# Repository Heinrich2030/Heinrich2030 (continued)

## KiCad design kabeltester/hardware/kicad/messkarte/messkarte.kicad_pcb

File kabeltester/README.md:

# Kabeltester – Tischgerät mit 7″-Touchdisplay

Kompakter Kabel- und Kabelbaumtester mit **128 Testpunkten (erweiterbar auf 256)**,
**4-Leiter-Widerstandsmessung bis 0,1 mΩ Auflösung** und großem Touchdisplay.
Jeder Testpunkt ist gleichzeitig Ein- und Ausgang – es gibt keine feste Aufteilung.

```
        ┌───────────────────────────────────────────┐
       ╱   [ A ▭▭▭▭▭▭▭▭ ]      [ B ▭▭▭▭▭▭▭▭ ]       ╱│   ← Adapterschächte (je 64 Pins)
      ╱───────────────────────────────────────────╱ │
     ╱  ┌─────────────────────────────┐   ( ● )  ╱  │   ← Start-Taster
    ╱   │   7″ Touch  800 × 480       │   ▮ ▮   ╱   │   ← Gut/Fehler-Leuchte
   ╱    │   GUT ✔  Cat6 1:1  2,1 s    │        ╱    │
  ╱     └─────────────────────────────┘       ╱    ╱
 └────────────────────────────────────────────┘   ╱      ca. 250 × 200 × 88 mm
 └────────────────────────────────────────────┘──╱
```

## Hardware-Auswahl (Kurzfassung)

| Baugruppe | Bauteil | Warum |
|---|---|---|
| Display + Bedienung | **Waveshare ESP32-S3-Touch-LCD-7** (7″, 800×480, kapazitiv) | großes Display, WLAN, 8 MB PSRAM, günstig (ca. 45 €) |
| Messsteuerung | **Raspberry Pi Pico 2 (RP2350)** | viele GPIO, schnelles SPI + ADC, ca. 6 € |
| Präzisionsmessung | **TI ADS1220** 24 Bit + **REF5025** | mΩ-Auflösung, 50/60-Hz-Filter, Temperatursensor |
| Testpunkt-Matrix | **ADG1606** (Force, 4,5 Ω) + **CD74HCT4067** (Sense) | echte 4-Leiter-Messung an jedem Pin |
| Adapter-Schnittstelle | **DIN 41612 C, 96-polig** | robust; 64 Testpunkte + Erkennung + I²C pro Seite |

Ausführliche Begründung, Schaltungskonzept und Leistungsdaten: [docs/hardware.md](docs/hardware.md).
Stückliste mit Bestellnummern: [hardware/stueckliste.csv](hardware/stueckliste.csv).

**Kosten (Richtwert):** ca. 330 € für den Grundausbau mit 128 Pins, ca. +190 € für den
Vollausbau mit 256 Pins, ca. 5–15 € je Steckeradapter.

## Funktionen

**Prüfen**
- Automatisches Erkennen der kompletten Verdrahtung (alle Pins gegen alle) in ca. 80 ms.
- **Einlernen mit Referenzkabel** („Golden Sample“): Kabel einstecken, Namen eingeben, fertig.
- Gut/Schlecht-Prüfung mit großer grün/roter Anzeige, Ton und LED-Leuchte.
- Fehlerarten im Klartext: *Unterbrechung, Kurzschluss, Vertauscht, Fehlverdrahtung,
  Widerstand zu hoch, hochohmiger Pfad (Feuchte/Schmutz), Diode/Halbleiter*.
- **Serienprüfung**: Kabel einstecken → Prüfung startet automatisch → abziehen → nächstes.
  Zähler für Gut/Fehler und Ausbeute in %.
- Start auch per Taster am Gerät oder **Fußschalter** (beide Hände frei).
- Optionale **Isolationsprüfung** zwischen allen Netzen (5 V, bis ca. 500 MΩ).

**Messen**
- 4-Leiter-Widerstandsmessung zwischen zwei beliebigen Pins, 0,1 mΩ … 200 kΩ, automatische
  Bereichswahl.
- **Stromumkehr**: hebt Thermospannungen auf und erkennt Dioden inkl. Polarität.
- **Längenberechnung** aus dem Widerstand (Kupfer, Querschnitt in mm² oder AWG),
  temperaturkompensiert über den Temperatursensor des ADC.
- **Nullabgleich** mit Kurzschlussadapter – Restwiderstände pro Pin werden gespeichert.

**Wackeltest**
- Überwacht alle gefundenen Verbindungen mit mehreren kHz und meldet jeden Aussetzer mit
  Dauer in µs – findet Wackelkontakte und Kabelbrüche, die beim normalen Test durchrutschen.

**Daten**
- Prüfprofile und Prüfprotokoll (CSV) im internen Flash.
- WLAN-Access-Point „Kabeltester“: Protokolle herunterladen, Profile hoch-/herunterladen im Browser.
- Profile als lesbare Textdateien, z. B.:
  ```
  KABELPROFIL 1
  name=Cat6 1:1
  pins=128
  durchgang=10
  isolation=10000000
  A1-B1 0.5
  A2-B2 0.5
  ```
- **Adapter-Erkennung**: Jeder Adapter trägt ein kleines EEPROM mit seinem Namen
  (z. B. „RJ45 8P8C“), der im Display angezeigt wird.
- **Fremdspannungsschutz**: Vor jeder Messung wird jeder Pin auf Spannung geprüft.

## Projektstruktur

```
kabeltester/
├── docs/hardware.md          Schaltungskonzept, Bauteilwahl, Leistungsdaten, Schutzkonzept
├── docs/adapter.md           Steckeradapter und Kurzschlussadapter bauen
├── hardware/stueckliste.csv  Stückliste mit Bestellnummern und Richtpreisen
├── hardware/kicad/           KiCad-Projekte: Schaltpläne, Platinen, Gerber, STEP (Generator in Python)
├── gehaeuse/step/            Gehäuse und Gesamtbaugruppe als STEP/STL (für jedes CAD-Programm)
├── gehaeuse/gehaeuse.scad    Pultgehäuse für den 3D-Druck (OpenSCAD, parametrisch)
├── docs/zusammenbau-3d.html  Drehbares 3D-Modell des Zusammenbaus mit Explosionsansicht (im Browser öffnen)
├── firmware/common/          Analyse-Kern (Soll/Ist-Vergleich, Profile, Länge) – auf PC testbar
├── firmware/messkarte/       Pico 2: Matrix, ADS1220, Messverfahren, Textprotokoll
├── firmware/display/         ESP32-S3: LVGL-Oberfläche, Profile, Protokoll, Weboberfläche
└── tests/                    PC-Tests für den Analyse-Kern
```

## Bauen und Flashen

Beide Firmwares sind PlatformIO-Projekte.

Messkarte (Pico 2 per USB im BOOTSEL-Modus anschließen):

```bash
cd kabeltester/firmware/messkarte && pio run -t upload
```

Display-Einheit: Zuerst `lvgl_port_v8.cpp` und `lvgl_port_v8.h` aus dem Waveshare-Beispiel
„lvgl_v8_port“ (Waveshare-Wiki zum ESP32-S3-Touch-LCD-7) nach `firmware/display/src/`
kopieren. Dann:

```bash
cd kabeltester/firmware/display && pio run -t upload
```

Tests des Analyse-Kerns auf dem PC:

```bash
make -C kabeltester/tests
```

Die Messkarte lässt sich auch ohne Display über USB bedienen (Terminal, 115 200 Baud), z. B.
`SCAN`, `R A1 B1`, `INFO`. Alle Befehle stehen am Anfang von
[`firmware/messkarte/src/main.cpp`](firmware/messkarte/src/main.cpp).

## Inbetriebnahme

1. Messkarte ohne Kanalkarten flashen, `INFO` per USB prüfen (Temperatur plausibel?).
2. Kanalkarten anschließen, `SCAN` ohne Adapter → keine Verbindungen.
3. Kurzschlussadapter auf Seite A und/oder B stecken → im Setup „Nullabgleich“ (oder `KAL NULL`).
   Jede Seite mit gestecktem Kurzschlussadapter wird einzeln abgeglichen, die anderen bleiben.
4. Präzisionswiderstände (z. B. 0,1 Ω / 10 Ω / 1 kΩ / 100 kΩ, 0,1 %) messen und mit den
   Leistungsdaten in `docs/hardware.md` vergleichen.

## Stand und offene Punkte

- Schaltpläne und Platinen-Platzierung in KiCad sind fertig, ebenso Gehäuse und Baugruppe als STEP.
  **Die Leiterbahnen fehlen noch** – siehe [hardware/kicad/README.md](hardware/kicad/README.md).
- Einige Pinbelegungen eigener Symbole und die DIN-41612-Ausrichtung sind vor der Bestellung zu prüfen
  (Liste in der KiCad-Anleitung).
- Die Firmware ist gegen die Bibliotheken syntaktisch geprüft, aber noch nicht auf echter Hardware
  gelaufen. Die Leistungsdaten sind berechnete Richtwerte.
- Die eingebauten LVGL-Schriften haben keine Umlaute; die Oberfläche schreibt daher „ue/oe“.

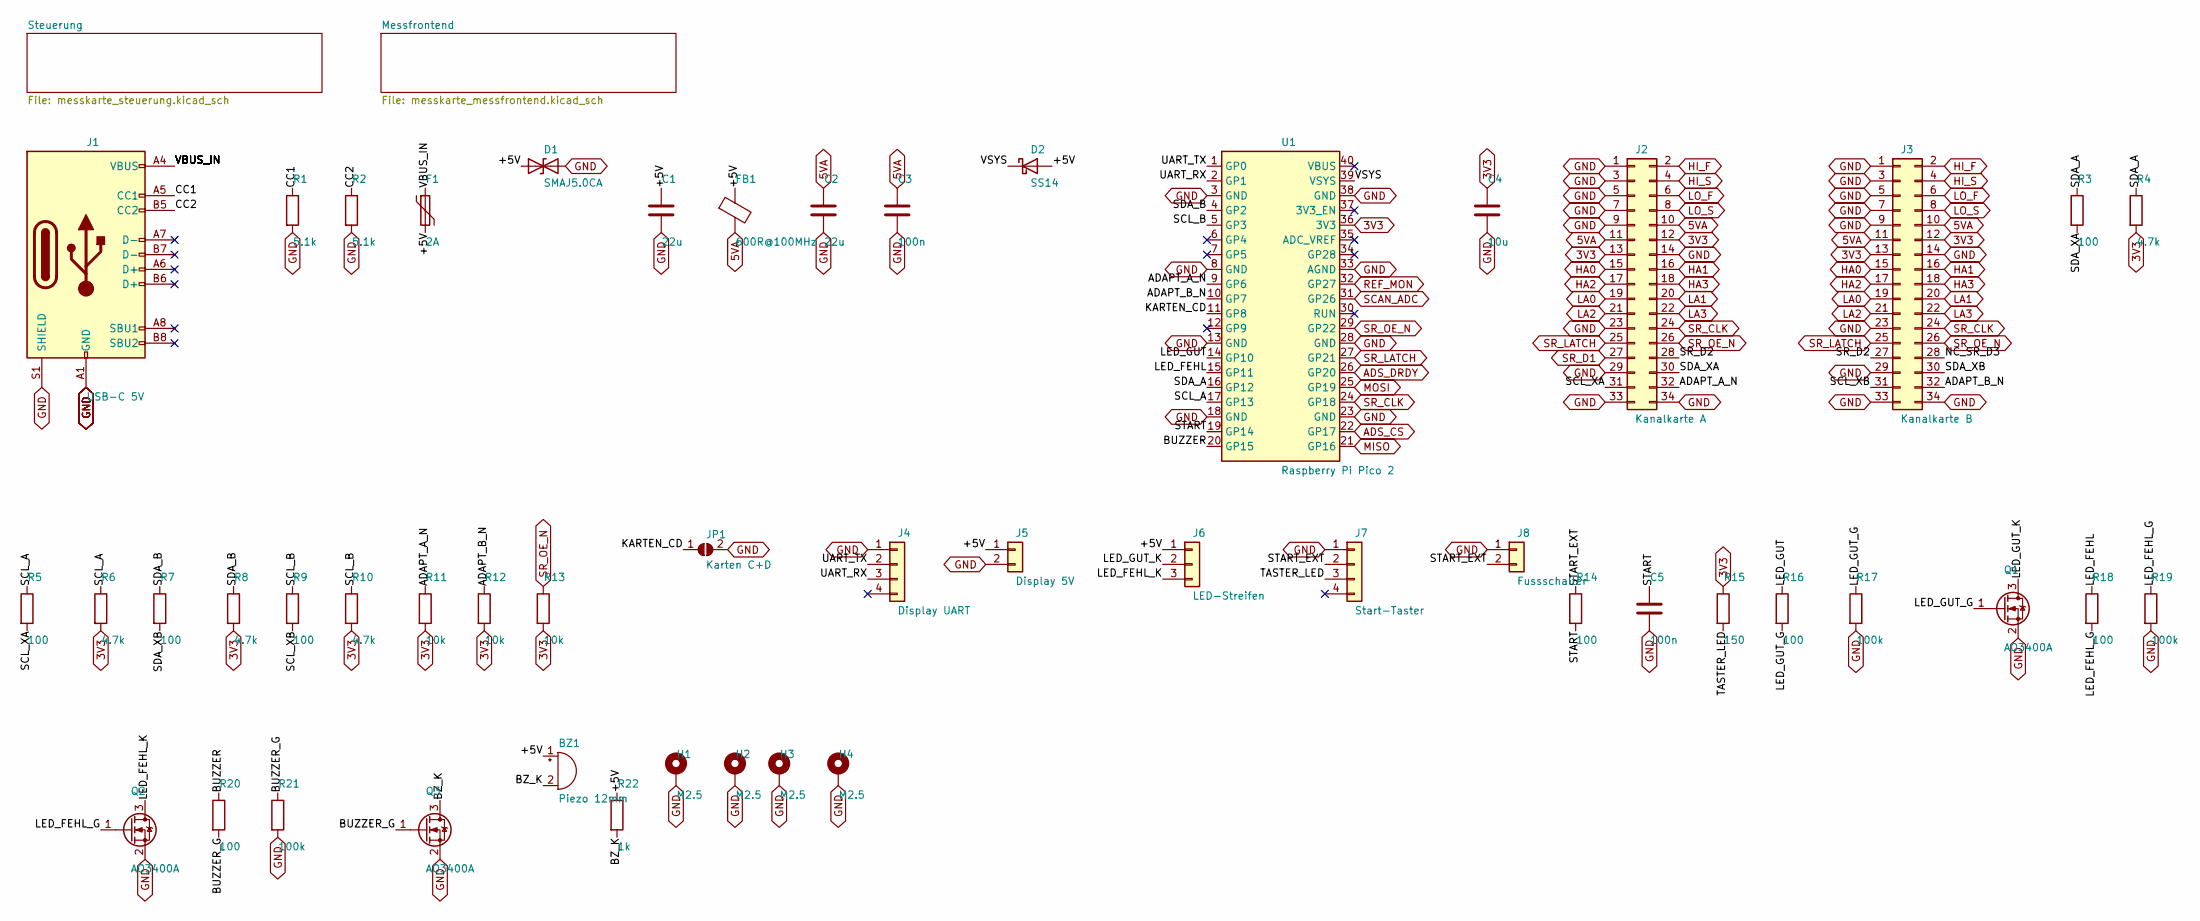
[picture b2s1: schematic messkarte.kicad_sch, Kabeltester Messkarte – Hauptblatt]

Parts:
BZ1: Piezo 12mm; Buzzer_12x9.5RM7.6; MPN TDK PS1240P02BT
C1, C2: 22u; C_1206_3216Metric
C3, C5: 100n; C_0603_1608Metric; LCSC C14663
C4: 10u; C_0805_2012Metric; LCSC C15850
D1: SMAJ5.0CA; D_SMA
D2: SS14; D_SMA; LCSC C2480
F1: 2A; Fuse_1812_4532Metric
FB1: 600R@100MHz; L_0805_2012Metric
H1, H2, H3, H4: M2.5; MountingHole_2.7mm_M2.5_Pad_Via
J1: USB-C 5V; USB_C_Receptacle_GCT_USB4105-xx-A_16P_TopMnt_Horizontal; MPN GCT USB4105-GF-A
J2: Kanalkarte A; IDC-Header_2x17_P2.54mm_Vertical
J3: Kanalkarte B; IDC-Header_2x17_P2.54mm_Vertical
J4: Display UART; JST_PH_B4B-PH-K_1x04_P2.00mm_Vertical
J5: Display 5V; JST_PH_B2B-PH-K_1x02_P2.00mm_Vertical
J6: LED-Streifen; JST_PH_B3B-PH-K_1x03_P2.00mm_Vertical
J7: Start-Taster; JST_PH_B4B-PH-K_1x04_P2.00mm_Vertical
J8: Fussschalter; JST_PH_B2B-PH-K_1x02_P2.00mm_Vertical
JP1: Karten C+D; SolderJumper-2_P1.3mm_Open_RoundedPad1.0x1.5mm
Q1, Q2, Q3: AO3400A; SOT-23; LCSC C20917
R1, R2: 5.1k; R_0603_1608Metric; LCSC C23186
R3, R5, R7, R9, R14, R16, R18, R20: 100; R_0603_1608Metric; LCSC C22775
R4, R6, R8, R10: 4.7k; R_0603_1608Metric; LCSC C23162
R11, R12, R13: 10k; R_0603_1608Metric; LCSC C25804
R15: 150; R_0603_1608Metric
R17, R19, R21: 100k; R_0603_1608Metric; LCSC C25803
R22: 1k; R_0603_1608Metric; LCSC C21190
U1: Raspberry Pi Pico 2; RaspberryPi_Pico2_THT; MPN Raspberry Pi SC1631

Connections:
3V3: C4.1, J2.12, J2.13, J3.12, J3.13, R4.2, R6.2, R8.2, R10.2, R11.2, R12.2, R13.2, R15.1, U1.36 (3V3); also elsewhere on the board
5VA: C2.1, C3.1, FB1.2, J2.10, J2.11, J3.10, J3.11; also elsewhere on the board
+5V: BZ1.1 (+), C1.1, D1.1 (A1), D2.2 (A), F1.2, FB1.1, J5.1, J6.1, R22.1
ADAPT_A_N: J2.32, R11.1, U1.9 (GP6)
ADAPT_B_N: J3.32, R12.1, U1.10 (GP7)
ADS_CS: U1.22 (GP17); also elsewhere on the board
ADS_DRDY: U1.26 (GP20); also elsewhere on the board
BUZZER: R20.1, U1.20 (GP15)
BUZZER_G: Q3.1 (G), R20.2, R21.1
BZ_K: BZ1.2 (-), Q3.3 (D), R22.2
CC1: J1.A5 (CC1), R1.1
CC2: J1.B5 (CC2), R2.1
GND: C1.2, C2.2, C3.2, C4.2, C5.2, D1.2 (A2), H1.1, H2.1, H3.1, H4.1, J1.A1 (GND), J1.A12 (GND), J1.B1 (GND), J1.B12 (GND), J1.S1 (SHIELD), J2.1, J2.3, J2.5, J2.7, J2.9, J2.14, J2.23, J2.29, J2.33, J2.34, J3.1, J3.3, J3.5, J3.7, J3.9, J3.14, J3.23, J3.29, J3.33, J3.34, J4.1, J5.2, J7.1, J8.1, JP1.2 (B), Q1.2 (S), Q2.2 (S), Q3.2 (S), R1.2, R2.2, R17.2, R19.2, R21.2, U1.3 (GND), U1.8 (GND), U1.13 (GND), U1.18 (GND), U1.23 (GND), U1.28 (GND), U1.33 (AGND), U1.38 (GND); also elsewhere on the board
HA0: J2.15, J3.15; also elsewhere on the board
HA1: J2.16, J3.16; also elsewhere on the board
HA2: J2.17, J3.17; also elsewhere on the board
HA3: J2.18, J3.18; also elsewhere on the board
HI_F: J2.2, J3.2; also elsewhere on the board
HI_S: J2.4, J3.4; also elsewhere on the board
KARTEN_CD: JP1.1 (A), U1.11 (GP8)
LA0: J2.19, J3.19; also elsewhere on the board
LA1: J2.20, J3.20; also elsewhere on the board
LA2: J2.21, J3.21; also elsewhere on the board
LA3: J2.22, J3.22; also elsewhere on the board
LED_FEHL: R18.1, U1.15 (GP11)
LED_FEHL_G: Q2.1 (G), R18.2, R19.1
LED_FEHL_K: J6.3, Q2.3 (D)
LED_GUT: R16.1, U1.14 (GP10)
LED_GUT_G: Q1.1 (G), R16.2, R17.1
LED_GUT_K: J6.2, Q1.3 (D)
LO_F: J2.6, J3.6; also elsewhere on the board
LO_S: J2.8, J3.8; also elsewhere on the board
MISO: U1.21 (GP16); also elsewhere on the board
MOSI: U1.25 (GP19); also elsewhere on the board
NC_SR_D3: J3.28
REF_MON: U1.32 (GP27); also elsewhere on the board
SCAN_ADC: U1.31 (GP26); also elsewhere on the board
SCL_A: R5.1, R6.1, U1.17 (GP13)
SCL_B: R9.1, R10.1, U1.5 (GP3)
SCL_XA: J2.31, R5.2
SCL_XB: J3.31, R9.2
SDA_A: R3.1, R4.1, U1.16 (GP12)
SDA_B: R7.1, R8.1, U1.4 (GP2)
SDA_XA: J2.30, R3.2
SDA_XB: J3.30, R7.2
SR_CLK: J2.24, J3.24, U1.24 (GP18); also elsewhere on the board
SR_D1: J2.27; also elsewhere on the board
SR_D2: J2.28, J3.27
SR_LATCH: J2.25, J3.25, U1.27 (GP21); also elsewhere on the board
SR_OE_N: J2.26, J3.26, R13.1, U1.29 (GP22); also elsewhere on the board
START: C5.1, R14.2, U1.19 (GP14)
START_EXT: J7.2, J8.2, R14.1
TASTER_LED: J7.3, R15.2
UART_RX: J4.3, U1.2 (GP1)
UART_TX: J4.2, U1.1 (GP0)
VBUS_IN: F1.1, J1.A4 (VBUS), J1.A9 (VBUS), J1.B4 (VBUS), J1.B9 (VBUS)
VSYS: D2.1 (K), U1.39 (VSYS)

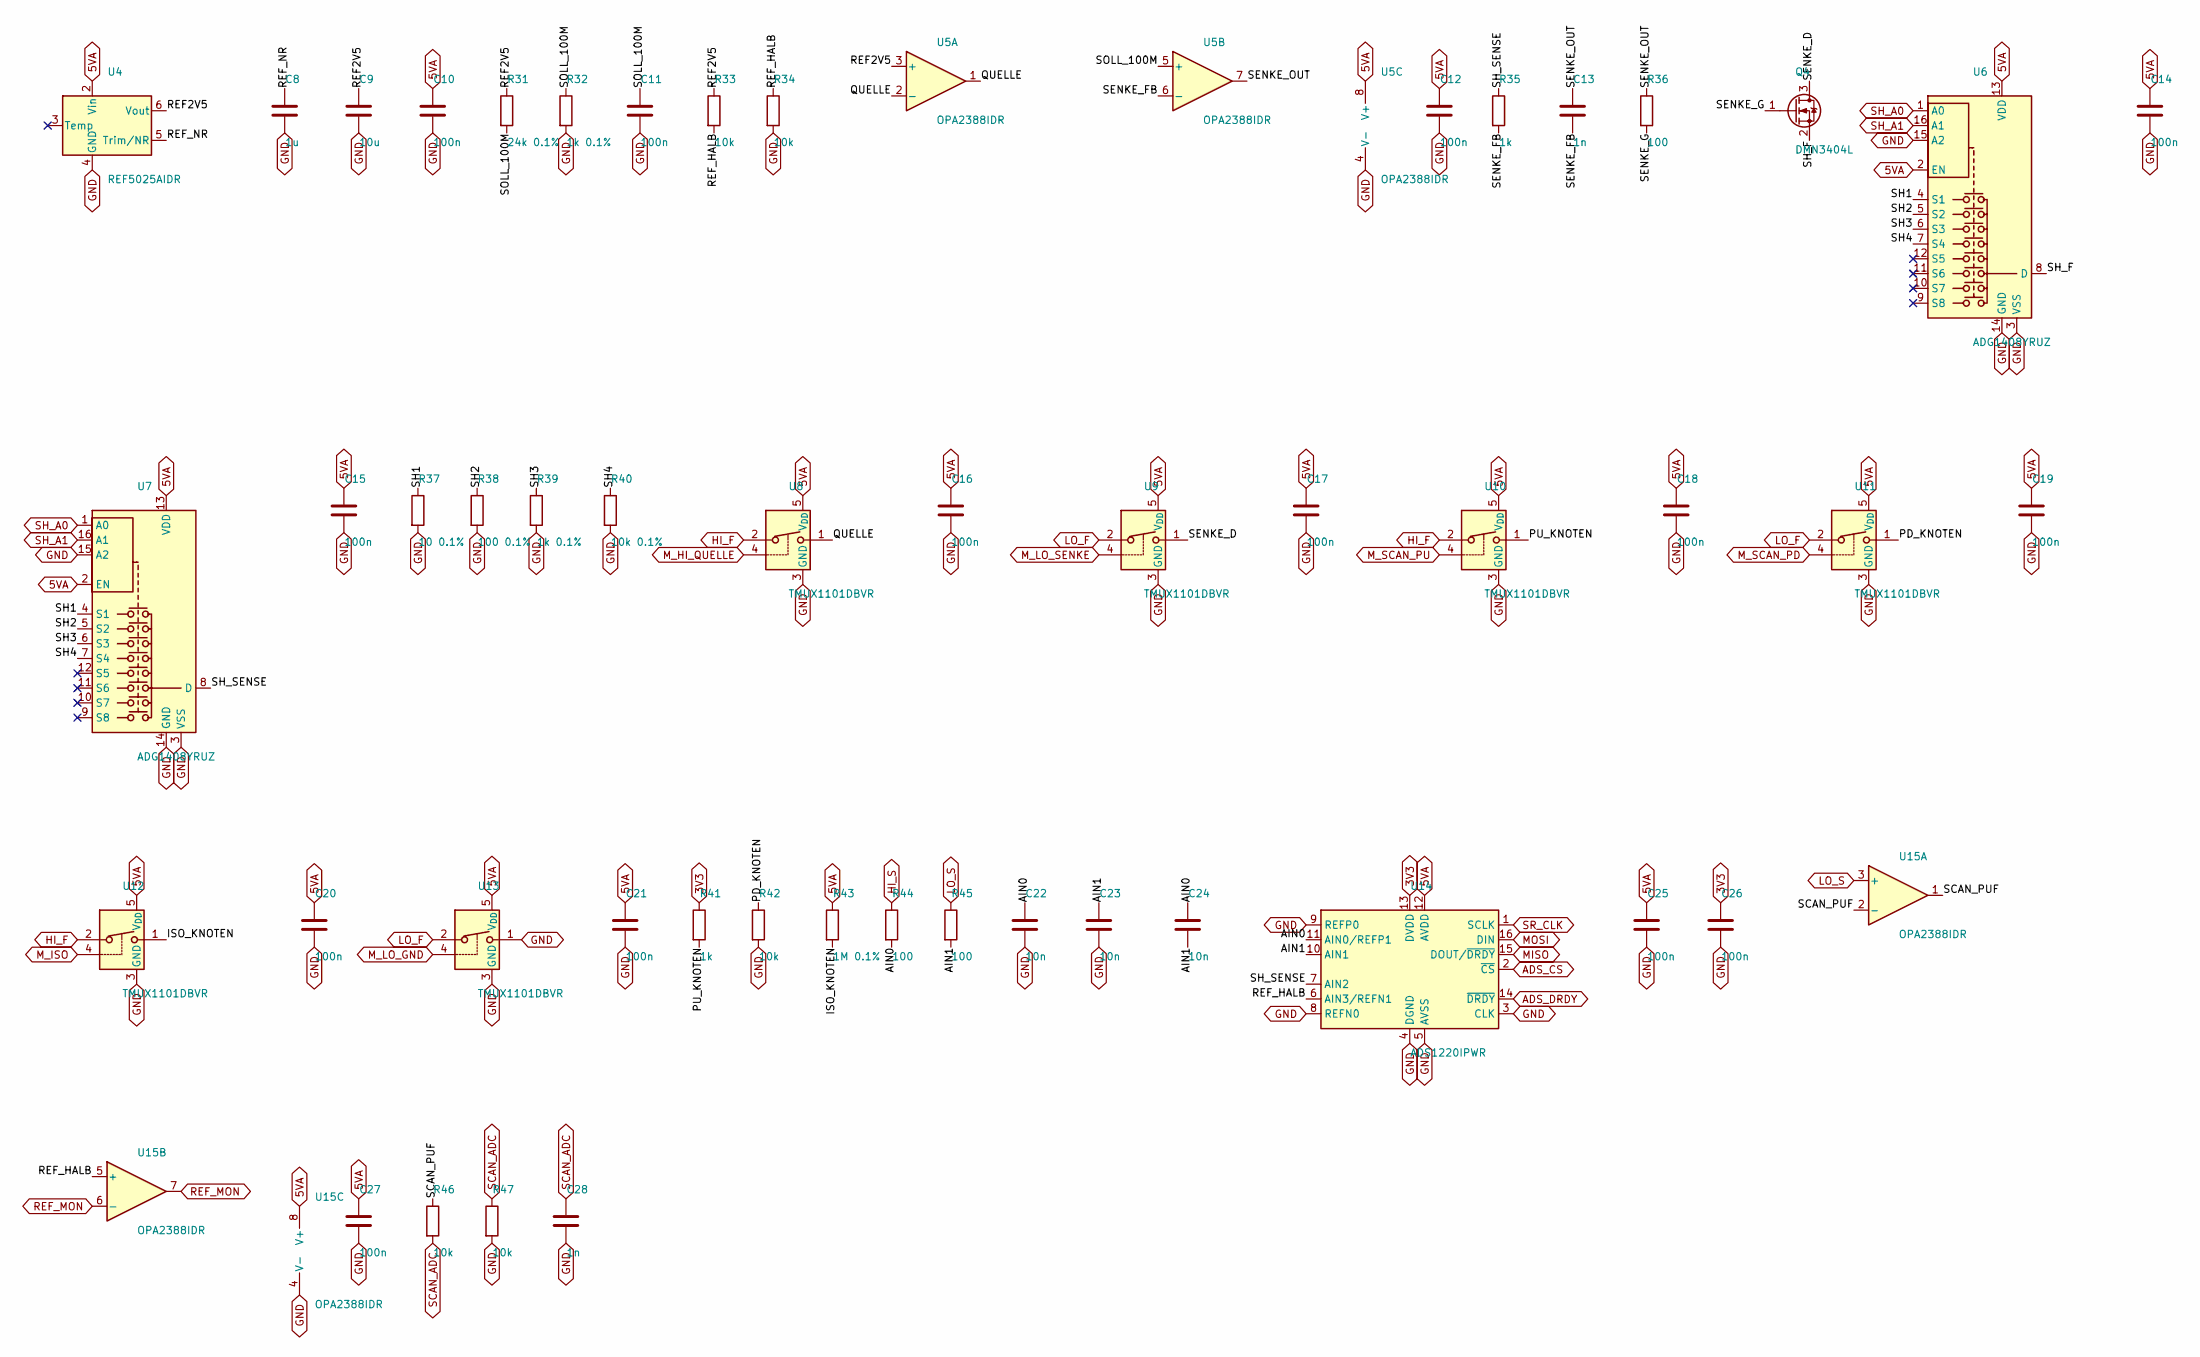
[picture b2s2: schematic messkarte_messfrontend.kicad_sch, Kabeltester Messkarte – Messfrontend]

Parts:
C8: 1u; C_0603_1608Metric; LCSC C15849
C9: 10u; C_0805_2012Metric; LCSC C15850
C10, C11, C12, C14, C15, C16, C17, C18, C19, C20, C21, C25, C26, C27: 100n; C_0603_1608Metric; LCSC C14663
C13, C28: 1n; C_0603_1608Metric; LCSC C1588
C22, C23, C24: 10n; C_0603_1608Metric; LCSC C57112
Q4: DMN3404L; SOT-23
R31: 24k 0.1%; R_0603_1608Metric
R32: 1k 0.1%; R_0603_1608Metric; LCSC C21190
R33, R34, R42, R46, R47: 10k; R_0603_1608Metric; LCSC C25804
R35, R41: 1k; R_0603_1608Metric; LCSC C21190
R36, R44, R45: 100; R_0603_1608Metric; LCSC C22775
R37: 10 0.1%; R_0805_2012Metric; MPN Vishay TNPW0805 0.1% 10ppm
R38: 100 0.1%; R_0805_2012Metric; MPN Vishay TNPW0805 0.1% 10ppm
R39: 1k 0.1%; R_0805_2012Metric; MPN Vishay TNPW0805 0.1% 10ppm
R40: 10k 0.1%; R_0805_2012Metric; MPN Vishay TNPW0805 0.1% 10ppm
R43: 1M 0.1%; R_0805_2012Metric; MPN Vishay TNPW08051M00BEEA
U4: REF5025AIDR; SOIC-8_3.9x4.9mm_P1.27mm
U5, U15: OPA2388IDR; SOIC-8_3.9x4.9mm_P1.27mm
U6, U7: ADG1408YRUZ; TSSOP-16_4.4x5mm_P0.65mm
U8, U9, U10, U11, U12, U13: TMUX1101DBVR; SOT-23-5
U14: ADS1220IPWR; TSSOP-16_4.4x5mm_P0.65mm

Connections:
3V3: C26.1, R41.1, U14.13 (DVDD); also elsewhere on the board
5VA: C10.1, C12.1, C14.1, C15.1, C16.1, C17.1, C18.1, C19.1, C20.1, C21.1, C25.1, C27.1, R43.1, U4.2 (Vin), U5.8 (V+), U6.2 (EN), U6.13 (VDD), U7.2 (EN), U7.13 (VDD), U8.5 (V_{DD}), U9.5 (V_{DD}), U10.5 (V_{DD}), U11.5 (V_{DD}), U12.5 (V_{DD}), U13.5 (V_{DD}), U14.12 (AVDD), U15.8 (V+); also elsewhere on the board
ADS_CS: U14.2 (~CS); also elsewhere on the board
ADS_DRDY: U14.14 (~DRDY); also elsewhere on the board
AIN0: C22.1, C24.1, R44.2, U14.11 (AIN0/REFP1)
AIN1: C23.1, C24.2, R45.2, U14.10 (AIN1)
GND: C8.2, C9.2, C10.2, C11.2, C12.2, C14.2, C15.2, C16.2, C17.2, C18.2, C19.2, C20.2, C21.2, C22.2, C23.2, C25.2, C26.2, C27.2, C28.2, R32.2, R34.2, R37.2, R38.2, R39.2, R40.2, R42.2, R47.2, U4.4 (GND), U5.4 (V-), U6.3 (VSS), U6.14 (GND), U6.15 (A2), U7.3 (VSS), U7.14 (GND), U7.15 (A2), U8.3 (GND), U9.3 (GND), U10.3 (GND), U11.3 (GND), U12.3 (GND), U13.1, U13.3 (GND), U14.3 (CLK), U14.4 (DGND), U14.5 (AVSS), U14.8 (REFN0), U14.9 (REFP0), U15.4 (V-); also elsewhere on the board
HI_F: U8.2, U10.2, U12.2; also elsewhere on the board
HI_S: R44.1; also elsewhere on the board
ISO_KNOTEN: R43.2, U12.1
LO_F: U9.2, U11.2, U13.2; also elsewhere on the board
LO_S: R45.1, U15.3 (+); also elsewhere on the board
MISO: U14.15 (DOUT/~DRDY); also elsewhere on the board
MOSI: U14.16 (DIN); also elsewhere on the board
M_HI_QUELLE: U8.4; also elsewhere on the board
M_ISO: U12.4; also elsewhere on the board
M_LO_GND: U13.4; also elsewhere on the board
M_LO_SENKE: U9.4; also elsewhere on the board
M_SCAN_PD: U11.4; also elsewhere on the board
M_SCAN_PU: U10.4; also elsewhere on the board
PD_KNOTEN: R42.1, U11.1
PU_KNOTEN: R41.2, U10.1
QUELLE: U5.1, U5.2 (-), U8.1
REF2V5: C9.1, R31.1, R33.1, U4.6 (Vout), U5.3 (+)
REF_HALB: R33.2, R34.1, U14.6 (AIN3/REFN1), U15.5 (+)
REF_MON: U15.6 (-), U15.7; also elsewhere on the board
REF_NR: C8.1, U4.5 (Trim/NR)
SCAN_ADC: C28.1, R46.2, R47.1; also elsewhere on the board
SCAN_PUF: R46.1, U15.1, U15.2 (-)
SENKE_D: Q4.3 (D), U9.1
SENKE_FB: C13.2, R35.2, U5.6 (-)
SENKE_G: Q4.1 (G), R36.2
SENKE_OUT: C13.1, R36.1, U5.7
SH1: R37.1, U6.4 (S1), U7.4 (S1)
SH2: R38.1, U6.5 (S2), U7.5 (S2)
SH3: R39.1, U6.6 (S3), U7.6 (S3)
SH4: R40.1, U6.7 (S4), U7.7 (S4)
SH_A0: U6.1 (A0), U7.1 (A0); also elsewhere on the board
SH_A1: U6.16 (A1), U7.16 (A1); also elsewhere on the board
SH_F: Q4.2 (S), U6.8 (D)
SH_SENSE: R35.1, U7.8 (D), U14.7 (AIN2)
SOLL_100M: C11.1, R31.2, R32.1, U5.5 (+)
SR_CLK: U14.1 (SCLK); also elsewhere on the board

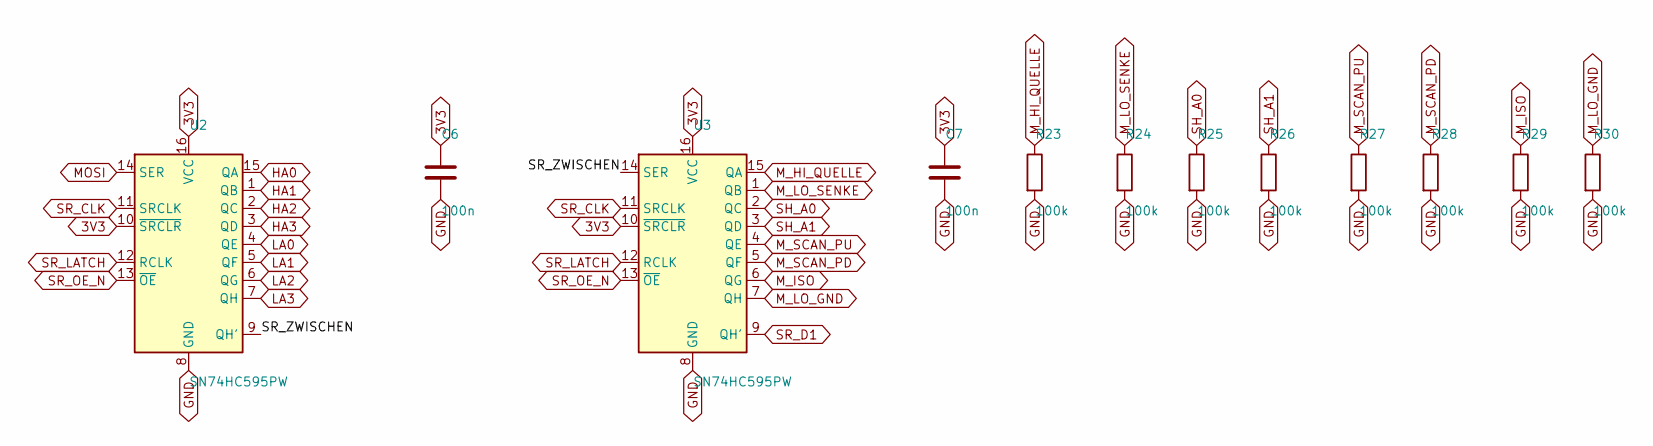
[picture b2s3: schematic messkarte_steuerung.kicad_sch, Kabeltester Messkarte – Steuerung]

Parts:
C6, C7: 100n; C_0603_1608Metric; LCSC C14663
R23, R24, R25, R26, R27, R28, R29, R30: 100k; R_0603_1608Metric; LCSC C25803
U2, U3: SN74HC595PW; TSSOP-16_4.4x5mm_P0.65mm; LCSC C5947

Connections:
3V3: C6.1, C7.1, U2.10 (~SRCLR), U2.16 (VCC), U3.10 (~SRCLR), U3.16 (VCC); also elsewhere on the board
GND: C6.2, C7.2, R23.2, R24.2, R25.2, R26.2, R27.2, R28.2, R29.2, R30.2, U2.8 (GND), U3.8 (GND); also elsewhere on the board
HA0: U2.15 (QA); also elsewhere on the board
HA1: U2.1 (QB); also elsewhere on the board
HA2: U2.2 (QC); also elsewhere on the board
HA3: U2.3 (QD); also elsewhere on the board
LA0: U2.4 (QE); also elsewhere on the board
LA1: U2.5 (QF); also elsewhere on the board
LA2: U2.6 (QG); also elsewhere on the board
LA3: U2.7 (QH); also elsewhere on the board
MOSI: U2.14 (SER); also elsewhere on the board
M_HI_QUELLE: R23.1, U3.15 (QA); also elsewhere on the board
M_ISO: R29.1, U3.6 (QG); also elsewhere on the board
M_LO_GND: R30.1, U3.7 (QH); also elsewhere on the board
M_LO_SENKE: R24.1, U3.1 (QB); also elsewhere on the board
M_SCAN_PD: R28.1, U3.5 (QF); also elsewhere on the board
M_SCAN_PU: R27.1, U3.4 (QE); also elsewhere on the board
SH_A0: R25.1, U3.2 (QC); also elsewhere on the board
SH_A1: R26.1, U3.3 (QD); also elsewhere on the board
SR_CLK: U2.11 (SRCLK), U3.11 (SRCLK); also elsewhere on the board
SR_D1: U3.9 (QH'); also elsewhere on the board
SR_LATCH: U2.12 (RCLK), U3.12 (RCLK); also elsewhere on the board
SR_OE_N: U2.13 (~OE), U3.13 (~OE); also elsewhere on the board
SR_ZWISCHEN: U2.9 (QH'), U3.14 (SER)

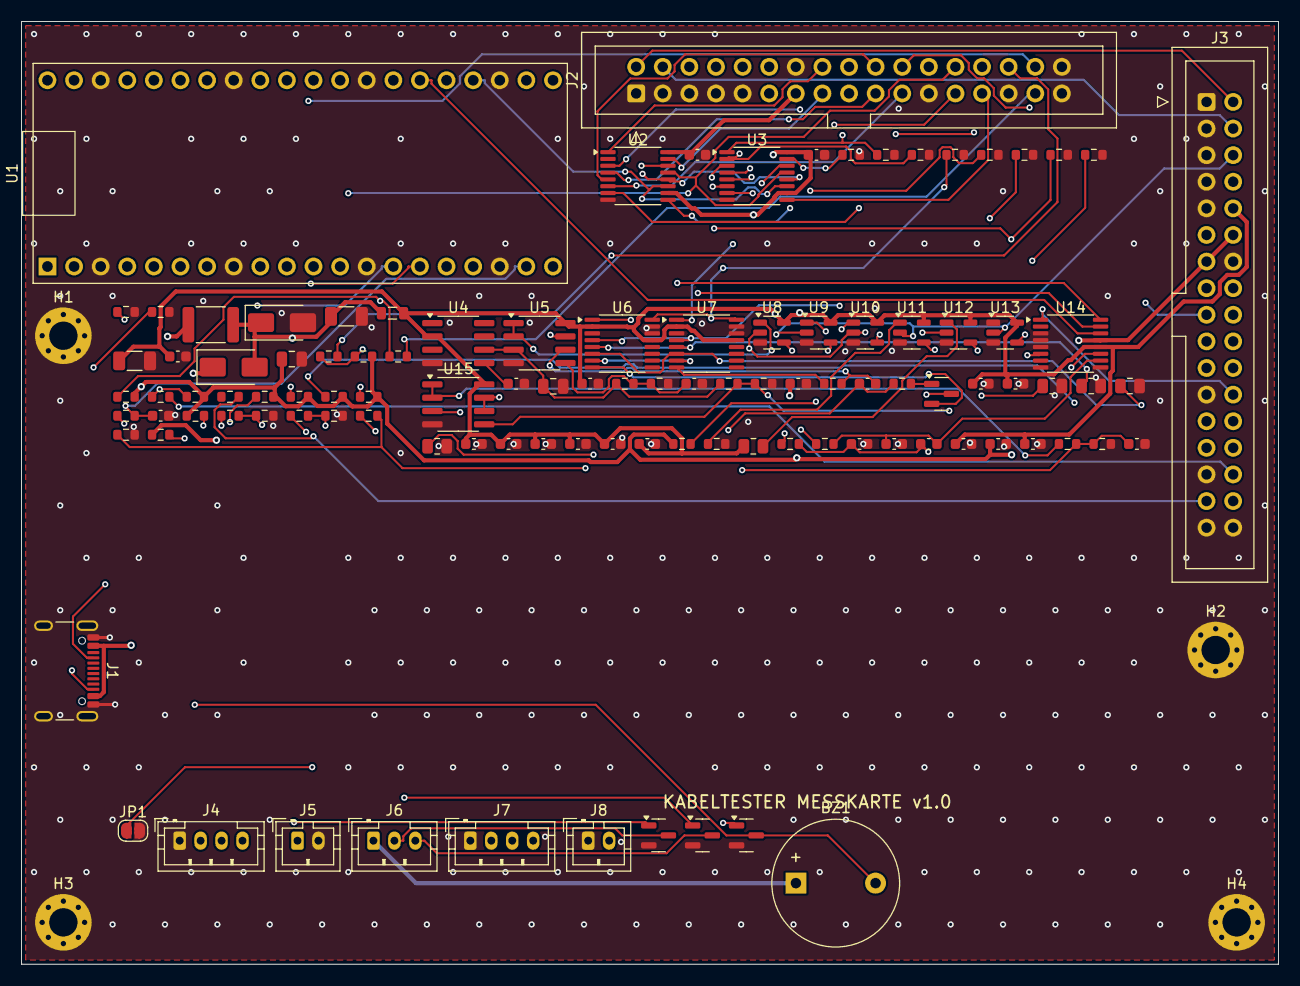
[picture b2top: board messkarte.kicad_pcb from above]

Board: 4 copper layers, 120.0 x 90.0 mm, 112 parts (0 on the bottom side), 86 nets.

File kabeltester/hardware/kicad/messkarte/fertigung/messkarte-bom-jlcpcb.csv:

Comment,Designator,Footprint,Menge,Hersteller-Nr.,LCSC Part #
Piezo 12mm,BZ1,Buzzer_12x9.5RM7.6,1,TDK PS1240P02BT,
100n,"C3,C5,C6,C7,C10,C11,C12,C14,C15,C16,C17,C18,C19,C20,C21,C25,C26,C27",C_0603_1608Metric,18,,C14663
10n,"C22,C23,C24",C_0603_1608Metric,3,,C57112
1n,"C13,C28",C_0603_1608Metric,2,,C1588
1u,C8,C_0603_1608Metric,1,,C15849
10u,"C4,C9",C_0805_2012Metric,2,,C15850
22u,"C1,C2",C_1206_3216Metric,2,,
Kanalkarte A,J2,IDC-Header_2x17_P2.54mm_Vertical,1,,
Kanalkarte B,J3,IDC-Header_2x17_P2.54mm_Vertical,1,,
Display 5V,J5,JST_PH_B2B-PH-K_1x02_P2.00mm_Vertical,1,,
Fussschalter,J8,JST_PH_B2B-PH-K_1x02_P2.00mm_Vertical,1,,
LED-Streifen,J6,JST_PH_B3B-PH-K_1x03_P2.00mm_Vertical,1,,
Display UART,J4,JST_PH_B4B-PH-K_1x04_P2.00mm_Vertical,1,,
Start-Taster,J7,JST_PH_B4B-PH-K_1x04_P2.00mm_Vertical,1,,
USB-C 5V,J1,USB_C_Receptacle_GCT_USB4105-xx-A_16P_TopMnt_Horizontal,1,GCT USB4105-GF-A,
SMAJ5.0CA,D1,D_SMA,1,,
SS14,D2,D_SMA,1,,C2480
2A,F1,Fuse_1812_4532Metric,1,,
600R@100MHz,FB1,L_0805_2012Metric,1,,
Karten C+D,JP1,SolderJumper-2_P1.3mm_Open_RoundedPad1.0x1.5mm,1,,
OPA2388IDR,"U5,U15",SOIC-8_3.9x4.9mm_P1.27mm,2,,
REF5025AIDR,U4,SOIC-8_3.9x4.9mm_P1.27mm,1,,
ADG1408YRUZ,"U6,U7",TSSOP-16_4.4x5mm_P0.65mm,2,,
ADS1220IPWR,U14,TSSOP-16_4.4x5mm_P0.65mm,1,,
SN74HC595PW,"U2,U3",TSSOP-16_4.4x5mm_P0.65mm,2,,C5947
AO3400A,"Q1,Q2,Q3",SOT-23,3,,C20917
DMN3404L,Q4,SOT-23,1,,
TMUX1101DBVR,"U8,U9,U10,U11,U12,U13",SOT-23-5,6,,
100,"R3,R5,R7,R9,R14,R16,R18,R20,R36,R44,R45",R_0603_1608Metric,11,,C22775
100k,"R17,R19,R21,R23,R24,R25,R26,R27,R28,R29,R30",R_0603_1608Metric,11,,C25803
10k,"R11,R12,R13,R33,R34,R42,R46,R47",R_0603_1608Metric,8,,C25804
150,R15,R_0603_1608Metric,1,,
1k,"R22,R35,R41",R_0603_1608Metric,3,,C21190
1k 0.1%,R32,R_0603_1608Metric,1,,C21190
24k 0.1%,R31,R_0603_1608Metric,1,,
4.7k,"R4,R6,R8,R10",R_0603_1608Metric,4,,C23162
5.1k,"R1,R2",R_0603_1608Metric,2,,C23186
10 0.1%,R37,R_0805_2012Metric,1,Vishay TNPW0805 0.1% 10ppm,
100 0.1%,R38,R_0805_2012Metric,1,Vishay TNPW0805 0.1% 10ppm,
10k 0.1%,R40,R_0805_2012Metric,1,Vishay TNPW0805 0.1% 10ppm,
1M 0.1%,R43,R_0805_2012Metric,1,Vishay TNPW08051M00BEEA,
1k 0.1%,R39,R_0805_2012Metric,1,Vishay TNPW0805 0.1% 10ppm,
Raspberry Pi Pico 2,U1,RaspberryPi_Pico2_THT,1,Raspberry Pi SC1631,

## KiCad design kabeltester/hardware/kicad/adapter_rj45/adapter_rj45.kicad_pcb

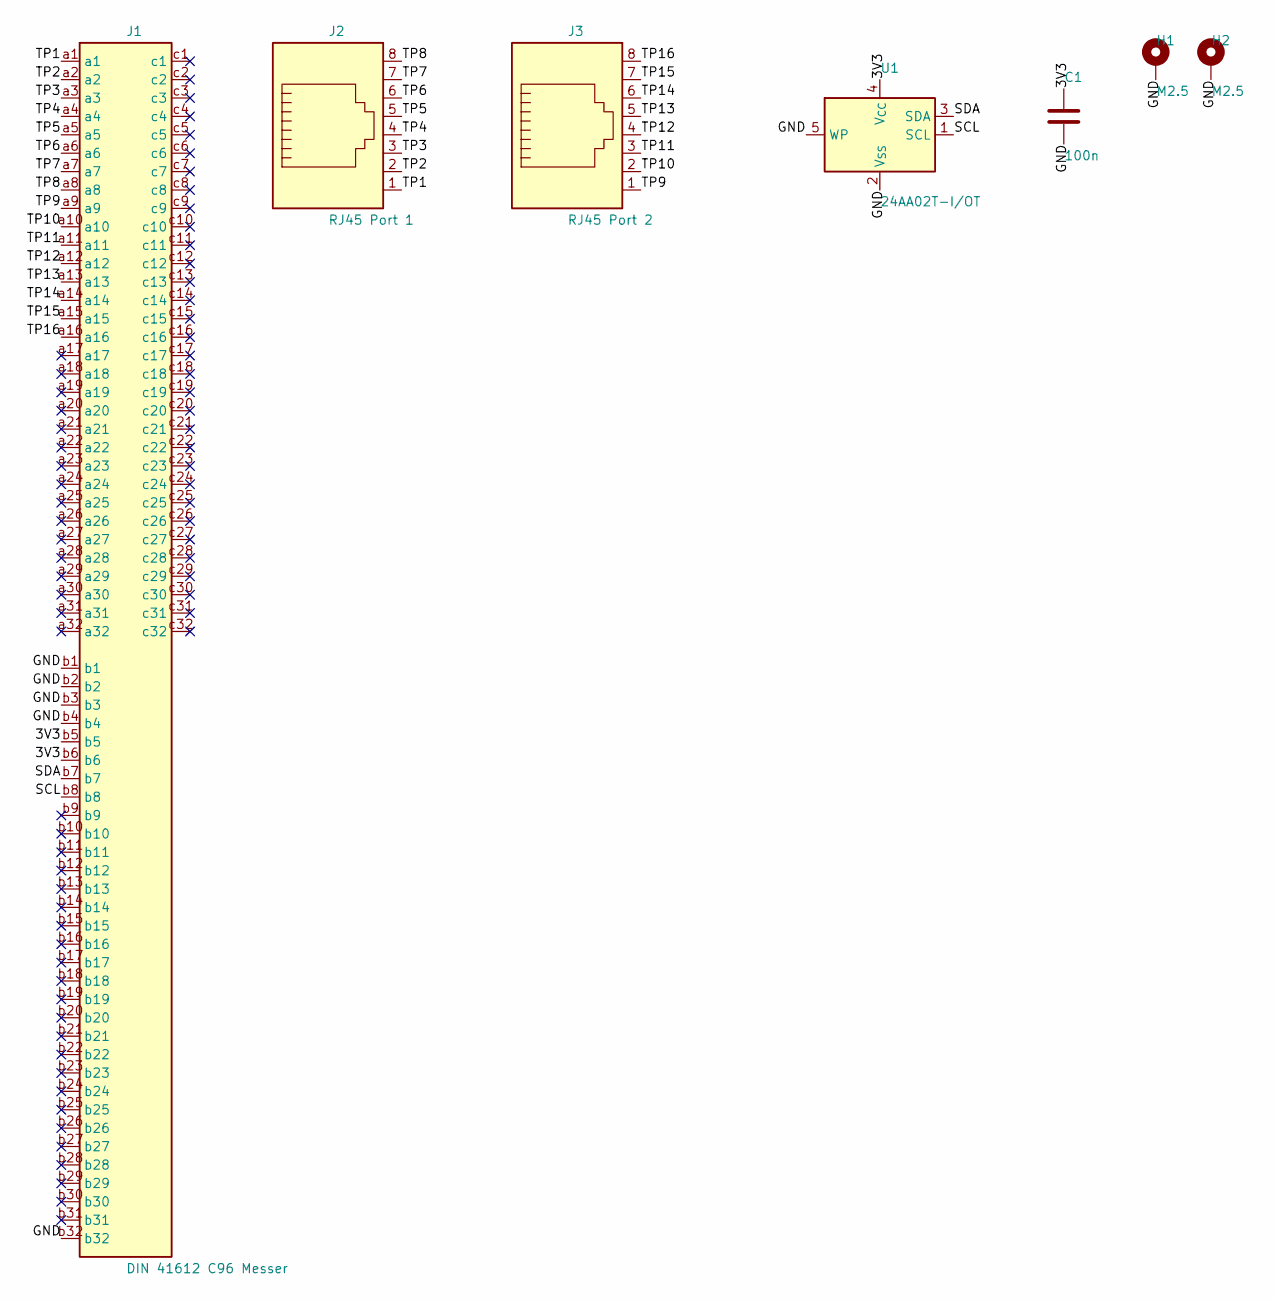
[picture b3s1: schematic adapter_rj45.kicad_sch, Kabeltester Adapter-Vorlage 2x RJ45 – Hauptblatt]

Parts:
C1: 100n; C_0603_1608Metric; LCSC C14663
H1, H2: M2.5; MountingHole_2.7mm_M2.5_Pad_Via
J1: DIN 41612 C96 Messer; DIN41612_C_3x32_Male_Horizontal_THT; MPN Harting DIN-Signal C096 M abgewinkelt
J2: RJ45 Port 1; RJ45_Amphenol_54602-x08_Horizontal; MPN Amphenol 54602-908LF
J3: RJ45 Port 2; RJ45_Amphenol_54602-x08_Horizontal; MPN Amphenol 54602-908LF
U1: 24AA02T-I/OT; SOT-23-5

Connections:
3V3: C1.1, J1.b5, J1.b6, U1.4 (V_{CC})
GND: C1.2, H1.1, H2.1, J1.b1, J1.b2, J1.b3, J1.b4, J1.b32, U1.2 (V_{SS}), U1.5 (WP)
SCL: J1.b8, U1.1 (SCL)
SDA: J1.b7, U1.3 (SDA)
TP1: J1.a1, J2.1
TP2: J1.a2, J2.2
TP3: J1.a3, J2.3
TP4: J1.a4, J2.4
TP5: J1.a5, J2.5
TP6: J1.a6, J2.6
TP7: J1.a7, J2.7
TP8: J1.a8, J2.8
TP9: J1.a9, J3.1
TP10: J1.a10, J3.2
TP11: J1.a11, J3.3
TP12: J1.a12, J3.4
TP13: J1.a13, J3.5
TP14: J1.a14, J3.6
TP15: J1.a15, J3.7
TP16: J1.a16, J3.8

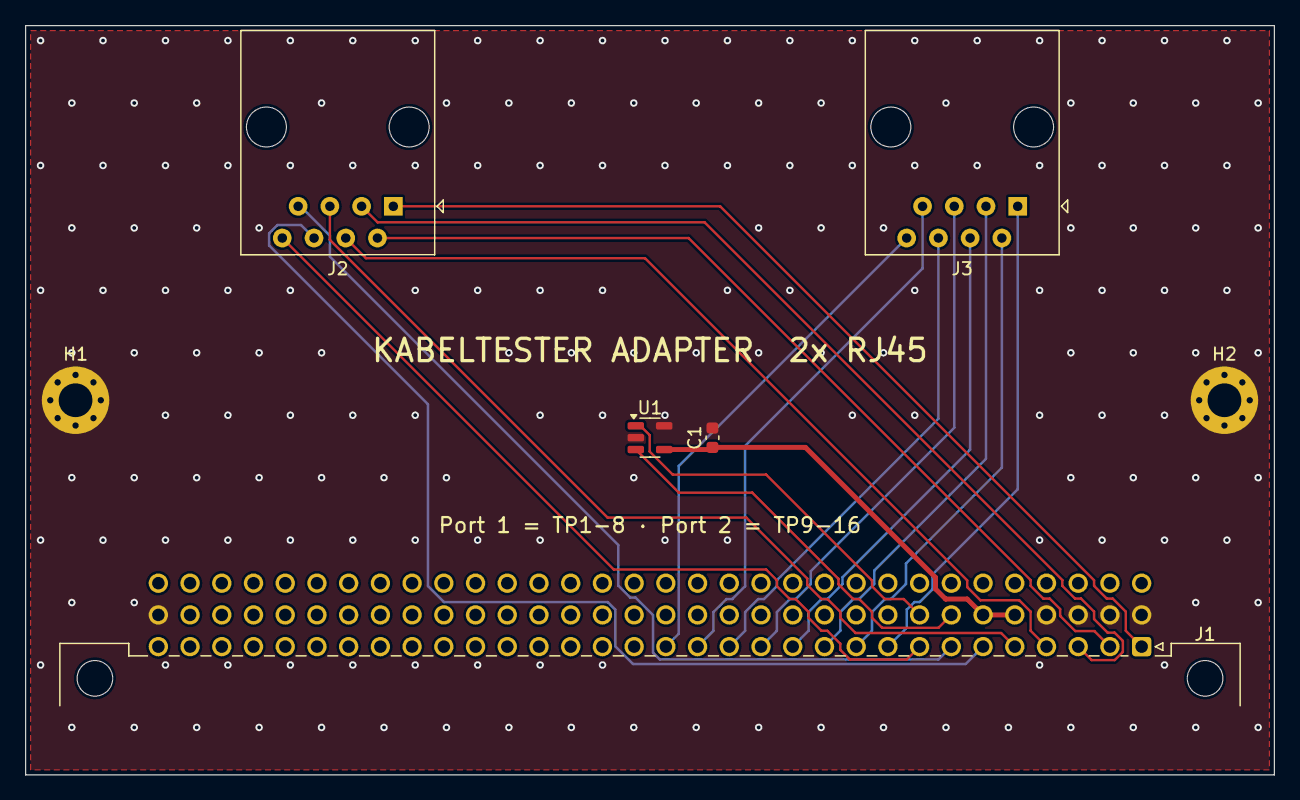
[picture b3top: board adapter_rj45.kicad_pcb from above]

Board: 2 copper layers, 100.0 x 60.0 mm, 7 parts (0 on the bottom side), 20 nets.

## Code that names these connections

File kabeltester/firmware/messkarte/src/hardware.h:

// Pinbelegung und Hardware-Konstanten der Messkarte (siehe docs/hardware.md)
#pragma once
#include <stdint.h>

namespace hw {

// --- SPI0: Schieberegister-Kette (74HC595) und ADS1220 -----------------------
constexpr uint8_t PIN_SPI_SCK   = 18;
constexpr uint8_t PIN_SPI_MOSI  = 19;
constexpr uint8_t PIN_SPI_MISO  = 16;
constexpr uint8_t PIN_ADS_CS    = 17;
constexpr uint8_t PIN_ADS_DRDY  = 20;
constexpr uint8_t PIN_595_LATCH = 21;
constexpr uint8_t PIN_595_OE    = 22;   // low = Ausgänge aktiv (Pull-up -> beim Start alles aus)

// --- Schnellscan: gepufferter LO-Sense-Bus am internen ADC ------------------
constexpr uint8_t PIN_SCAN_ADC  = 26;   // ADC0
constexpr uint8_t PIN_VBUS_ADC  = 27;   // ADC1: Monitor REF5025/2 über OPV-Puffer (Selbsttest)

// --- UART zum Display (ESP32-S3) ------------------------------------------
constexpr uint8_t PIN_UART_TX   = 0;
constexpr uint8_t PIN_UART_RX   = 1;
constexpr uint32_t UART_BAUD    = 921600;

// --- I²C zu den Adapter-EEPROMs (Reihe b der DIN-41612-Leisten) -------------
// Je Seite ein eigener Bus: alle Adapter-EEPROMs (24AA02, SOT-23) haben die feste Adresse 0x50.
constexpr uint8_t PIN_I2C_A_SDA = 12;   // I2C0 -> Kanalkarte A
constexpr uint8_t PIN_I2C_A_SCL = 13;
constexpr uint8_t PIN_I2C_B_SDA = 2;    // I2C1 -> Kanalkarte B
constexpr uint8_t PIN_I2C_B_SCL = 3;
constexpr uint8_t ADAPTER_EEPROM = 0x50;

// --- Bedienung / Signalisierung ---------------------------------------------
constexpr uint8_t PIN_START     = 14;   // Start-Taster / Fußschalter (gegen GND)
constexpr uint8_t PIN_BUZZER    = 15;
constexpr uint8_t PIN_LED_GUT   = 10;   // grüner LED-Streifen über MOSFET
constexpr uint8_t PIN_LED_FEHL  = 11;   // roter LED-Streifen über MOSFET
constexpr uint8_t PIN_ADAPT_A   = 6;    // Adapter steckt in Seite A (Kontakt b32 -> GND)
constexpr uint8_t PIN_ADAPT_B   = 7;
constexpr uint8_t PIN_KARTEN_CD = 8;    // Brücke nach GND = Erweiterungskarten C+D gesteckt

// --- Kanalkarten -------------------------------------------------------------
constexpr int PINS_PRO_KARTE  = 64;     // 4 Blöcke à 16
constexpr int MAX_KARTEN      = 4;      // 2 = Grundausbau (A+B), 4 = Vollausbau (256 Pins)

// --- Schieberegister-Kette (Reihenfolge = zuerst geschobenes Byte zuletzt) ---
// Byte 0: Adressen  [3:0] HI-Kanal, [7:4] LO-Kanal (gemeinsam für Force+Sense)
// Byte 1: Modus-Bits des Mess-Frontends
// Byte 2+2k: Force-Enables Karte k  [3:0] HI-Block 0..3, [7:4] LO-Block 0..3 (ADG1606, aktiv high)
// Byte 3+2k: Sense-Enables Karte k  gleiche Bitlage (CD74HCT4067, aktiv low -> Firmware invertiert)
constexpr uint8_t MODUS_HI_QUELLE   = 1 << 0;  // HI-Force -> 2,500-V-Quelle (REF5025 + Puffer)
constexpr uint8_t MODUS_LO_SENKE    = 1 << 1;  // LO-Force -> Präzisions-Stromsenke
constexpr uint8_t MODUS_SHUNT_MASK  = 3 << 2;  // Shunt-Auswahl im Regelkreis (ADG1404)
constexpr uint8_t MODUS_SCAN_PU     = 1 << 4;  // HI-Force -> 3,3 V über 1 kΩ
constexpr uint8_t MODUS_SCAN_PD     = 1 << 5;  // LO-Force -> GND über 10 kΩ
constexpr uint8_t MODUS_ISO         = 1 << 6;  // HI-Force -> AVDD über 1 MΩ (0,1 %)
constexpr uint8_t MODUS_LO_GND      = 1 << 7;  // LO-Force -> GND (niederohmig)

// Strombereiche: Sollspannung 100 mV am Shunt -> I = 0,1 V / R_shunt
struct Bereich { float strom; float shunt; uint8_t bits; };
constexpr Bereich BEREICHE[] = {
  {10e-3f,  10.0f,    0 << 2},   // 0 … ~120 Ω (Spannungsreserve), Auflösung 0,1 mΩ
  {1e-3f,   100.0f,   1 << 2},   // … 2 kΩ
  {100e-6f, 1000.0f,  2 << 2},   // … 20 kΩ
  {10e-6f,  10000.0f, 3 << 2},   // … 200 kΩ
};
constexpr int ANZAHL_BEREICHE = 4;

constexpr float R_ISO        = 1.0e6f;   // Referenz für Isolationsmessung
constexpr float SCAN_SCHWELLE = 0.55f;   // Anteil von 3,3 V: > Schwelle = Verbindung (< ca. 7 kΩ)
constexpr float FREMD_MAX_V   = 0.30f;   // ab hier Fremdspannung -> Abbruch

}  // namespace hw

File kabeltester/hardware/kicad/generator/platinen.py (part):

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    force = {15: 'ENF_HI0', 1: 'ENF_HI1', 2: 'ENF_HI2', 3: 'ENF_HI3', 4: 'ENF_LO0', 5: 'ENF_LO1', 6: 'ENF_LO2', 7: 'ENF_LO3'}
    sense = {15: 'ENS_HI0_N', 1: 'ENS_HI1_N', 2: 'ENS_HI2_N', 3: 'ENS_HI3_N', 4: 'ENS_LO0_N', 5: 'ENS_LO1_N', 6: 'ENS_LO2_N', 7: 'ENS_LO3_N'}
    for ausg, ser, qh in ((force, 'SR_DIN', 'SR_MITTE'), (sense, 'SR_MITTE', 'SR_DOUT')):
        pins = {16: '3V3', 8: 'GND', 10: '3V3', 11: 'SR_CLK', 12: 'SR_LATCH', 13: 'SR_OE_N', 14: ser, 9: qh}
        pins.update(ausg)
        p.teil('U', '74xx:74HC595', 'SN74HC595PW', TSSOP16, pins, LCSC='C5947')
        p.entkoppeln('3V3')
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    adr = {15: 'HA0', 1: 'HA1', 2: 'HA2', 3: 'HA3', 4: 'LA0', 5: 'LA1', 6: 'LA2', 7: 'LA3'}
    modus = {15: 'M_HI_QUELLE', 1: 'M_LO_SENKE', 2: 'SH_A0', 3: 'SH_A1', 4: 'M_SCAN_PU', 5: 'M_SCAN_PD', 6: 'M_ISO', 7: 'M_LO_GND'}
    for ausg, ser, qh in ((adr, 'MOSI', 'SR_ZWISCHEN'), (modus, 'SR_ZWISCHEN', 'SR_D1')):
        pins = {16: '3V3', 8: 'GND', 10: '3V3', 11: 'SR_CLK', 12: 'SR_LATCH', 13: 'SR_OE_N', 14: ser, 9: qh}
        pins.update(ausg)
        p.teil('U', '74xx:74HC595', 'SN74HC595PW', TSSOP16, pins, LCSC='C5947')
        p.entkoppeln('3V3')
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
